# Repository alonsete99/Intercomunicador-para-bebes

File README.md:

# Intercomunicador para bebes
 TFG

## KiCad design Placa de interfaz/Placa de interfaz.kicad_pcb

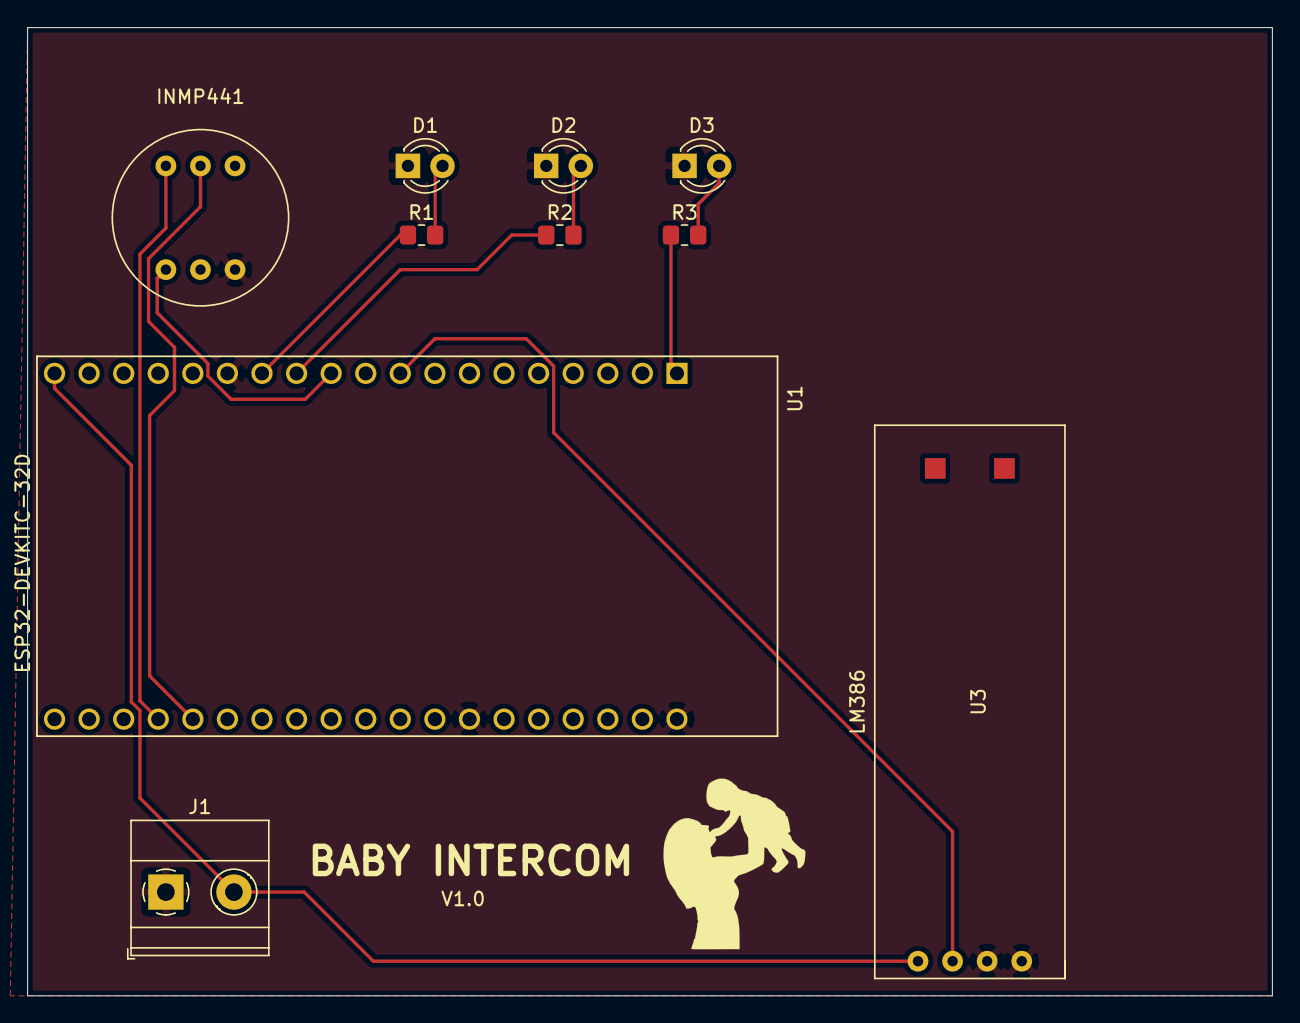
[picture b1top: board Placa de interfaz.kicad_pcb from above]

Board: 2 copper layers, 91.4 x 71.1 mm, 10 parts (0 on the bottom side), 12 nets.

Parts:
D1, D2, D3: LED; LED_D3.0mm_IRGrey
J1: Conn_01x02_Female; TerminalBlock_Phoenix_MKDS-1,5-2_1x02_P5.00mm_Horizontal
R1, R2, R3: 1k; R_0805_2012Metric_Pad1.20x1.40mm_HandSolder
U1: ESP32-DEVKITC-32D; MODULE_ESP32-DEVKITC-32D
U2: INMP441
U3: LM386; lm386_amplifier

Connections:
+3V3: R3.1, U1.1, U2.2
+5V: J1.2, U1.19, U3.4
/LED1: R1.1, U1.13
/LED2: R2.1, U1.12
/OUTPUT_SOUND: U1.9, U3.3
/SCK: U1.35, U2.6
/SD: U1.11, U2.3
/SW: U1.34, U2.5
GND: D1.1, D2.1, D3.1, J1.1, U1.14, U1.20, U1.26, U2.1, U3.1, U3.2
unnamed: D1.2, R1.2
unnamed: D2.2, R2.2
unnamed: D3.2, R3.2

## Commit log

2022-02-01 Subida de archivos
